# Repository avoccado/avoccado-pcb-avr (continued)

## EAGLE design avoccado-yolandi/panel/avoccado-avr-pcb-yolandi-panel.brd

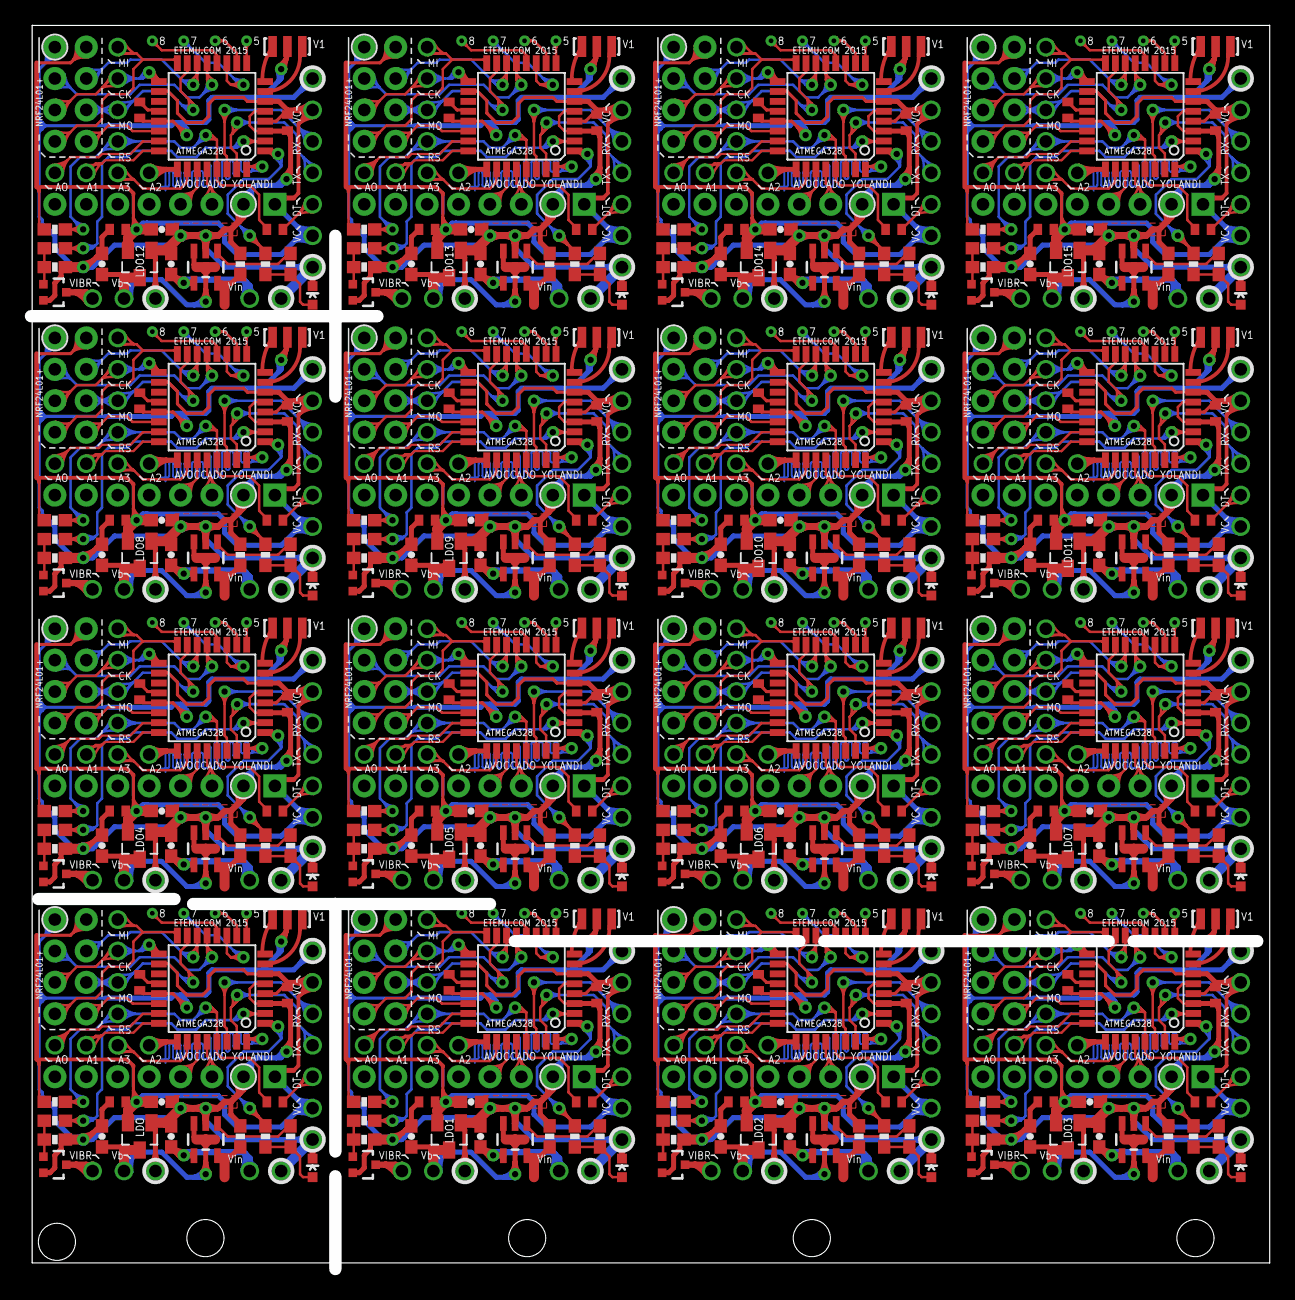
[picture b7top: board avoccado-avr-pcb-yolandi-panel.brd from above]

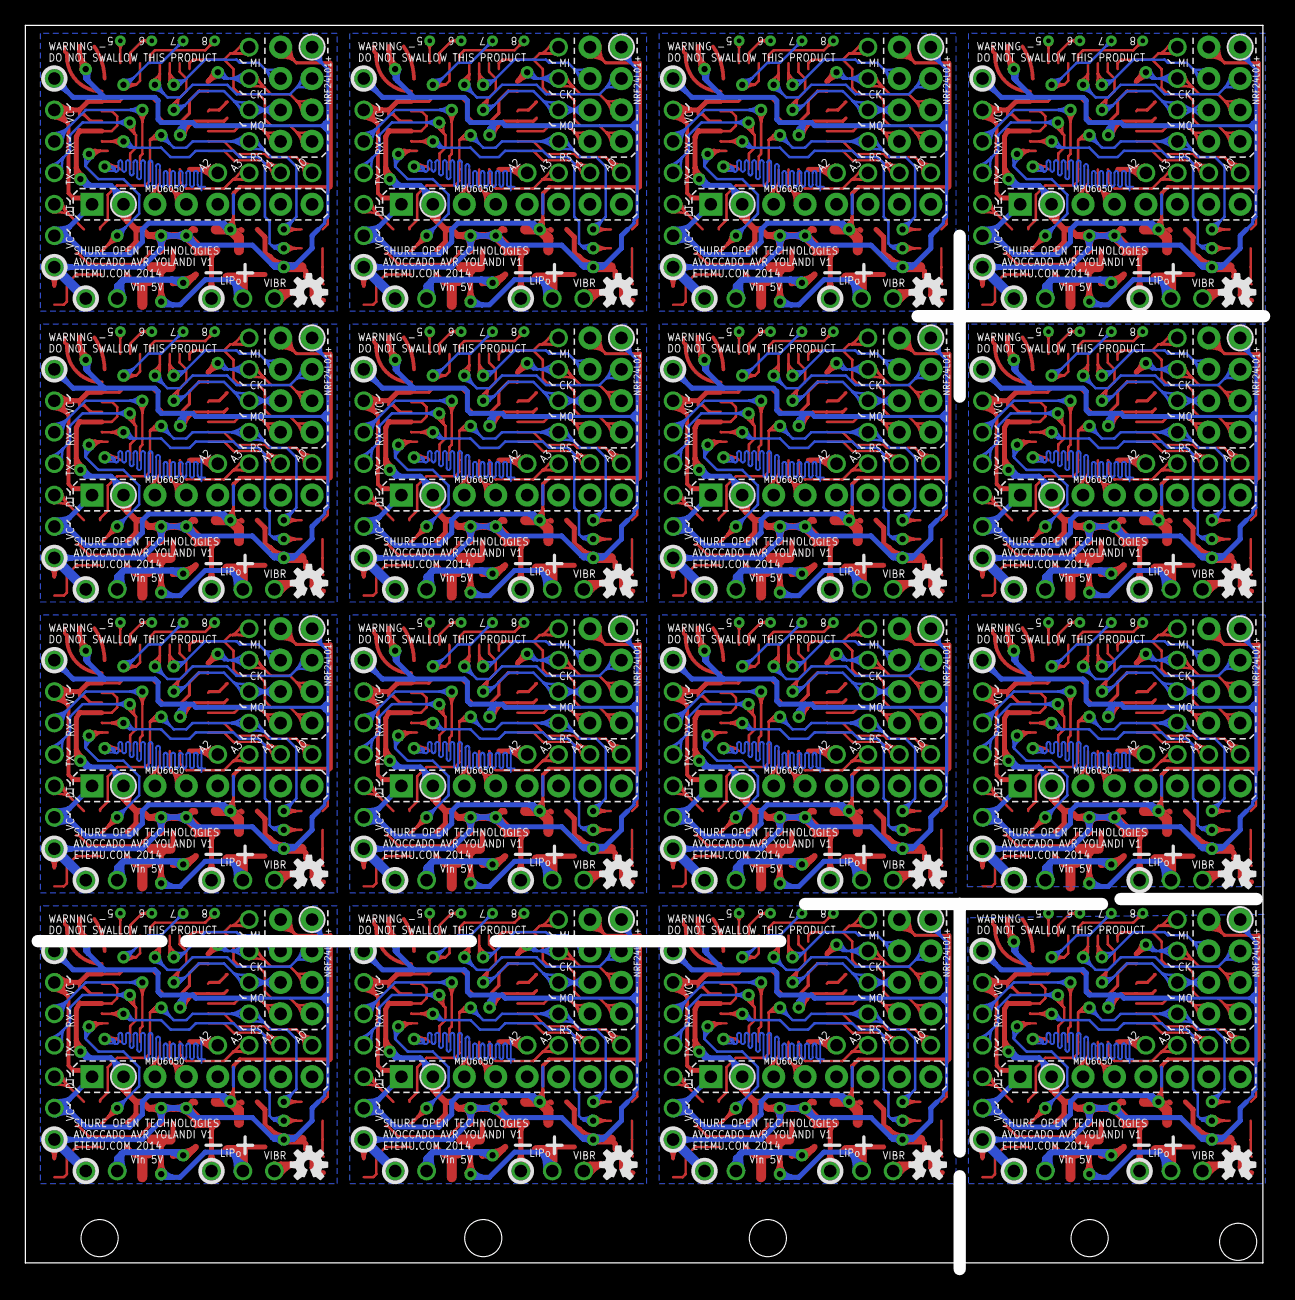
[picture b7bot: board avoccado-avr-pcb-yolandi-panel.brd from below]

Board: 2 copper layers, 99.6 x 100.0 mm, 784 parts (16 on the bottom side), 544 nets.

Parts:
AVR, AVR1, AVR2, AVR3, AVR4, AVR5, AVR6, AVR7, AVR8, AVR9, AVR10, AVR11, AVR12, AVR13, AVR14, AVR15: ATMEGA328P; TQFP32-08
C1, C2, C3, C7, C8, C9, C10, C12, C15, C16, C17, C19, C22, C23, C24, C26, C29, C30, C31, C33, C36, C37, C38, C40, C43, C44, C45, C47, C50, C51, C52, C54, C57, C58, C59, C61, C64, C65, C66, C68, C71, C72, C73, C75, C78, C79, C80, C82, C85, C86, C87, C89, C92, C93, C94, C96, C99, C100, C101, C103, C106, C107, C108, C110: 0.1uF; C0402
C4, C5, C6, C11, C13, C14, C18, C20, C21, C25, C27, C28, C32, C34, C35, C39, C41, C42, C46, C48, C49, C53, C55, C56, C60, C62, C63, C67, C69, C70, C74, C76, C77, C81, C83, C84, C88, C90, C91, C95, C97, C98, C102, C104, C105, C109, C111, C112: 4.7uF; 0603-CAP
D1, D2, D3, D4, D5, D6, D7, D8, D9, D10, D11, D12, D13, D14, D15, D16: LED; LED-0603
JP1, JP4, JP51, JP76, JP101, JP126, JP151, JP176, JP201, JP226, JP251, JP276, JP301, JP326, JP351, JP376: MPU6050; 1X08_PIN1_NO_SILK
JP2, JP27, JP28, JP29, JP47, JP48, JP49, JP50, JP72, JP73, JP74, JP75, JP97, JP98, JP99, JP100, JP122, JP123, JP124, JP125, JP147, JP148, JP149, JP150, JP172, JP173, JP174, JP175, JP197, JP198, JP199, JP200, JP222, JP223, JP224, JP225, JP247, JP248, JP249, JP250, JP272, JP273, JP274, JP275, JP297, JP298, JP299, JP300, JP322, JP323, JP324, JP325, JP347, JP348, JP349, JP350, JP372, JP373, JP374, JP375, JP397, JP398, JP399, JP400: M021X02_NO_SILK; 1X02_NO_SILK
JP3, JP5, JP6, JP7, JP8, JP9, JP10, JP11, JP12, JP13, JP14, JP15, JP16, JP17, JP18, JP19, JP20, JP21, JP22, JP23, JP24, JP25, JP26, JP30, JP31, JP32, JP33, JP34, JP35, JP36, JP37, JP38, JP39, JP40, JP41, JP42, JP43, JP44, JP45, JP46, JP52, JP53, JP54, JP55, JP56, JP57, JP58, JP59, JP60, JP61, JP62, JP63, JP64, JP65, JP66, JP67, JP68, JP69, JP70, JP71, JP77, JP78, JP79, JP80, JP81, JP82, JP83, JP84, JP85, JP86, JP87, JP88, JP89, JP90, JP91, JP92, JP93, JP94, JP95, JP96, JP102, JP103, JP104, JP105, JP106, JP107, JP108, JP109, JP110, JP111, JP112, JP113, JP114, JP115, JP116, JP117, JP118, JP119, JP120, JP121, JP127, JP128, JP129, JP130, JP131, JP132, JP133, JP134, JP135, JP136, JP137, JP138, JP139, JP140, JP141, JP142, JP143, JP144, JP145, JP146, JP152, JP153, JP154, JP155, JP156, JP157, JP158, JP159, JP160, JP161, JP162, JP163, JP164, JP165, JP166, JP167, JP168, JP169, JP170, JP171, JP177, JP178, JP179, JP180, JP181, JP182, JP183, JP184, JP185, JP186, JP187, JP188, JP189, JP190, JP191, JP192, JP193, JP194, JP195, JP196, JP202, JP203, JP204, JP205, JP206, JP207, JP208, JP209, JP210, JP211, JP212, JP213, JP214, JP215, JP216, JP217, JP218, JP219, JP220, JP221, JP227, JP228, JP229, JP230, JP231, JP232, JP233, JP234, JP235, JP236, JP237, JP238, JP239, JP240, JP241, JP242, JP243, JP244, JP245, JP246, JP252, JP253, JP254, JP255, JP256, JP257, JP258, JP259, JP260, JP261, JP262, JP263, JP264, JP265, JP266, JP267, JP268, JP269, JP270, JP271, JP277, JP278, JP279, JP280, JP281, JP282, JP283, JP284, JP285, JP286, JP287, JP288, JP289, JP290, JP291, JP292, JP293, JP294, JP295, JP296, JP302, JP303, JP304, JP305, JP306, JP307, JP308, JP309, JP310, JP311, JP312, JP313, JP314, JP315, JP316, JP317, JP318, JP319, JP320, JP321, JP327, JP328, JP329, JP330, JP331, JP332, JP333, JP334, JP335, JP336, JP337, JP338, JP339, JP340, JP341, JP342, JP343, JP344, JP345, JP346, JP352, JP353, JP354, JP355, JP356, JP357, JP358, JP359, JP360, JP361, JP362, JP363, JP364, JP365, JP366, JP367, JP368, JP369, JP370, JP371, JP377, JP378, JP379, JP380, JP381, JP382, JP383, JP384, JP385, JP386, JP387, JP388, JP389, JP390, JP391, JP392, JP393, JP394, JP395, JP396: M01NOSILK-KIT; 1X01NS-KIT
LDO, LDO1, LDO2, LDO3, LDO4, LDO5, LDO6, LDO7, LDO8, LDO9, LDO10, LDO11, LDO12, LDO13, LDO14, LDO15: MCP1703CB; SOT23
LOGO1, LOGO2, LOGO3, LOGO4, LOGO5, LOGO6, LOGO7, LOGO8, LOGO9, LOGO10, LOGO11, LOGO12, LOGO13, LOGO14, LOGO15, LOGO16: OSHW-LOGOS; OSHW-LOGO-S
Q1, Q3, Q5, Q7, Q9, Q11, Q13, Q15, Q17, Q19, Q21, Q23, Q25, Q27, Q29, Q31: 16MHz; RESONATOR-SMD
Q2, Q4, Q6, Q8, Q10, Q12, Q14, Q16, Q18, Q20, Q22, Q24, Q26, Q28, Q30, Q32: FET; SOT323
R1, R4, R6, R8, R10, R12, R14, R16, R18, R20, R22, R24, R26, R28, R30, R32, R34, R36, R38, R40, R42, R44, R46, R48, R50, R52, R54, R56, R58, R60, R62, R64, R66, R68, R70, R72, R74, R76, R78, R80, R82, R84, R86, R88, R90, R92, R94, R96: 1K; 0603-RES
R2, R7, R13, R19, R25, R31, R37, R43, R49, R55, R61, R67, R73, R79, R85, R91: 10K; 0603-RES
R3, R9, R15, R21, R27, R33, R39, R45, R51, R57, R63, R69, R75, R81, R87, R93: Rchg; 0603-RES
R5, R11, R17, R23, R29, R35, R41, R47, R53, R59, R65, R71, R77, R83, R89, R95: 1M; 0603-RES
TP1, TP2, TP3, TP4, TP5, TP6, TP7, TP8, TP9, TP10, TP11, TP12, TP13, TP14, TP15, TP16, TP17, TP18, TP19, TP20, TP21, TP22, TP23, TP24, TP25, TP26, TP27, TP28, TP29, TP30, TP31, TP32, TP33, TP34, TP35, TP36, TP37, TP38, TP39, TP40, TP41, TP42, TP43, TP44, TP45, TP46, TP47, TP48, TP49, TP50, TP51, TP52, TP53, TP54, TP55, TP56, TP57, TP58, TP59, TP60, TP61, TP62, TP63, TP64: TEST-POINTTP_15TH_THRU; TP_15TH
U1, U2, U3, U4, U5, U6, U7, U8, U9, U10, U11, U12, U13, U14, U15, U16: MCP73831; SOT23-5

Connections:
3.3V: AVR.4, AVR.6, AVR.18, C3.2, C6.1, C10.1, JP1.1, JP2.2, JP11.1, JP18.1, LDO.2, R2.2
3.3V1: AVR1.4, AVR1.6, AVR1.18, C7.1, C8.2, C14.1, JP4.1, JP31.1, JP38.1, JP47.2, LDO1.2, R7.2
3.3V2: AVR2.4, AVR2.6, AVR2.18, C15.1, C16.2, C21.1, JP51.1, JP56.1, JP63.1, JP72.2, LDO2.2, R13.2
3.3V3: AVR3.4, AVR3.6, AVR3.18, C22.1, C23.2, C28.1, JP76.1, JP81.1, JP88.1, JP97.2, LDO3.2, R19.2
3.3V4: AVR4.4, AVR4.6, AVR4.18, C29.1, C30.2, C35.1, JP101.1, JP106.1, JP113.1, JP122.2, LDO4.2, R25.2
3.3V5: AVR5.4, AVR5.6, AVR5.18, C36.1, C37.2, C42.1, JP126.1, JP131.1, JP138.1, JP147.2, LDO5.2, R31.2
3.3V6: AVR6.4, AVR6.6, AVR6.18, C43.1, C44.2, C49.1, JP151.1, JP156.1, JP163.1, JP172.2, LDO6.2, R37.2
3.3V7: AVR7.4, AVR7.6, AVR7.18, C50.1, C51.2, C56.1, JP176.1, JP181.1, JP188.1, JP197.2, LDO7.2, R43.2
3.3V8: AVR8.4, AVR8.6, AVR8.18, C57.1, C58.2, C63.1, JP201.1, JP206.1, JP213.1, JP222.2, LDO8.2, R49.2
3.3V9: AVR9.4, AVR9.6, AVR9.18, C64.1, C65.2, C70.1, JP226.1, JP231.1, JP238.1, JP247.2, LDO9.2, R55.2
3.3V10: AVR10.4, AVR10.6, AVR10.18, C71.1, C72.2, C77.1, JP251.1, JP256.1, JP263.1, JP272.2, LDO10.2, R61.2
3.3V11: AVR11.4, AVR11.6, AVR11.18, C78.1, C79.2, C84.1, JP276.1, JP281.1, JP288.1, JP297.2, LDO11.2, R67.2
3.3V12: AVR12.4, AVR12.6, AVR12.18, C85.1, C86.2, C91.1, JP301.1, JP306.1, JP313.1, JP322.2, LDO12.2, R73.2
3.3V13: AVR13.4, AVR13.6, AVR13.18, C92.1, C93.2, C98.1, JP326.1, JP331.1, JP338.1, JP347.2, LDO13.2, R79.2
3.3V14: AVR14.4, AVR14.6, AVR14.18, C99.1, C100.2, C105.1, JP351.1, JP356.1, JP363.1, JP372.2, LDO14.2, R85.2
3.3V15: AVR15.4, AVR15.6, AVR15.18, C106.1, C107.2, C112.1, JP376.1, JP381.1, JP388.1, JP397.2, LDO15.2, R91.2
5V: C4.1, JP17.1, U2.4
5V1: C11.1, JP37.1, U1.4
5V2: C18.1, JP62.1, U3.4
5V3: C25.1, JP87.1, U4.4
5V4: C32.1, JP112.1, U5.4
5V5: C39.1, JP137.1, U6.4
5V6: C46.1, JP162.1, U7.4
5V7: C53.1, JP187.1, U8.4
5V8: C60.1, JP212.1, U9.4
5V9: C67.1, JP237.1, U10.4
5V10: C74.1, JP262.1, U11.4
5V11: C81.1, JP287.1, U12.4
5V12: C88.1, JP312.1, U13.4
5V13: C95.1, JP337.1, U14.4
5V14: C102.1, JP362.1, U15.4
5V15: C109.1, JP387.1, U16.4
A0: AVR.23, JP19.1
A1: AVR.24, JP20.1
A2: AVR.25, JP21.1
A3: AVR.26, JP22.1
A4: AVR.27, JP1.4
A5: AVR.28, JP1.3
A7: AVR1.28, JP4.3
A7-NRF-IRQ: AVR.22, JP29.2
A7-NRF-IRQ1: AVR1.22, JP50.2
A7-NRF-IRQ2: AVR2.22, JP75.2
A7-NRF-IRQ3: AVR3.22, JP100.2
A7-NRF-IRQ4: AVR4.22, JP125.2
A7-NRF-IRQ5: AVR5.22, JP150.2
A7-NRF-IRQ6: AVR6.22, JP175.2
A7-NRF-IRQ7: AVR7.22, JP200.2
A7-NRF-IRQ8: AVR8.22, JP225.2
A7-NRF-IRQ9: AVR9.22, JP250.2
A7-NRF-IRQ10: AVR10.22, JP275.2
A7-NRF-IRQ11: AVR11.22, JP300.2
A7-NRF-IRQ12: AVR12.22, JP325.2
A7-NRF-IRQ13: AVR13.22, JP350.2
A7-NRF-IRQ14: AVR14.22, JP375.2
A7-NRF-IRQ15: AVR15.22, JP400.2
A8: AVR1.27, JP4.4
A9: AVR1.26, JP42.1
A10: AVR1.25, JP41.1
A11: AVR1.24, JP40.1
A12: AVR1.23, JP39.1
A14: AVR2.28, JP51.3
A15: AVR2.27, JP51.4
A16: AVR2.26, JP67.1
A17: AVR2.25, JP66.1
A18: AVR2.24, JP65.1
A19: AVR2.23, JP64.1
A21: AVR3.28, JP76.3
A22: AVR3.27, JP76.4
A23: AVR3.26, JP92.1
A24: AVR3.25, JP91.1
A25: AVR3.24, JP90.1
A26: AVR3.23, JP89.1
A28: AVR4.28, JP101.3
A29: AVR4.27, JP101.4
A30: AVR4.26, JP117.1
A31: AVR4.25, JP116.1
A32: AVR4.24, JP115.1
A33: AVR4.23, JP114.1
A35: AVR5.28, JP126.3
A36: AVR5.27, JP126.4
A37: AVR5.26, JP142.1
A38: AVR5.25, JP141.1
A39: AVR5.24, JP140.1
A40: AVR5.23, JP139.1
A42: AVR6.28, JP151.3
A43: AVR6.27, JP151.4
A44: AVR6.26, JP167.1
A45: AVR6.25, JP166.1
A46: AVR6.24, JP165.1
A47: AVR6.23, JP164.1
A49: AVR7.28, JP176.3
A50: AVR7.27, JP176.4
A51: AVR7.26, JP192.1
A52: AVR7.25, JP191.1
A53: AVR7.24, JP190.1
A54: AVR7.23, JP189.1
A56: AVR8.28, JP201.3
A57: AVR8.27, JP201.4
A58: AVR8.26, JP217.1
A59: AVR8.25, JP216.1
A60: AVR8.24, JP215.1
A61: AVR8.23, JP214.1
A63: AVR9.28, JP226.3
A64: AVR9.27, JP226.4
A65: AVR9.26, JP242.1
A66: AVR9.25, JP241.1
A67: AVR9.24, JP240.1
A68: AVR9.23, JP239.1
A70: AVR10.28, JP251.3
A71: AVR10.27, JP251.4
A72: AVR10.26, JP267.1
A73: AVR10.25, JP266.1
A74: AVR10.24, JP265.1
A75: AVR10.23, JP264.1
A77: AVR11.28, JP276.3
A78: AVR11.27, JP276.4
A79: AVR11.26, JP292.1
A80: AVR11.25, JP291.1
A81: AVR11.24, JP290.1
A82: AVR11.23, JP289.1
A84: AVR12.28, JP301.3
A85: AVR12.27, JP301.4
A86: AVR12.26, JP317.1
A87: AVR12.25, JP316.1
A88: AVR12.24, JP315.1
A89: AVR12.23, JP314.1
A91: AVR13.28, JP326.3
A92: AVR13.27, JP326.4
A93: AVR13.26, JP342.1
A94: AVR13.25, JP341.1
A95: AVR13.24, JP340.1
A96: AVR13.23, JP339.1
A98: AVR14.28, JP351.3
A99: AVR14.27, JP351.4
A100: AVR14.26, JP367.1
A101: AVR14.25, JP366.1
A102: AVR14.24, JP365.1
A103: AVR14.23, JP364.1
A105: AVR15.28, JP376.3
A106: AVR15.27, JP376.4
A107: AVR15.26, JP392.1
A108: AVR15.25, JP391.1
A109: AVR15.24, JP390.1
A110: AVR15.23, JP389.1
AREF: AVR.20, C1.2
AREF1: AVR1.20, C9.2
AREF2: AVR2.20, C17.2
AREF3: AVR3.20, C24.2
AREF4: AVR4.20, C31.2
AREF5: AVR5.20, C38.2
AREF6: AVR6.20, C45.2
AREF7: AVR7.20, C52.2
AREF8: AVR8.20, C59.2
AREF9: AVR9.20, C66.2
AREF10: AVR10.20, C73.2
AREF11: AVR11.20, C80.2
AREF12: AVR12.20, C87.2
AREF13: AVR13.20, C94.2
AREF14: AVR14.20, C101.2
AREF15: AVR15.20, C108.2
CHG-PROG: R3.2, U2.5
CHG-PROG1: R9.2, U1.5
CHG-PROG2: R15.2, U3.5
CHG-PROG3: R21.2, U4.5
CHG-PROG4: R27.2, U5.5
CHG-PROG5: R33.2, U6.5
CHG-PROG6: R39.2, U7.5
CHG-PROG7: R45.2, U8.5
CHG-PROG8: R51.2, U9.5
CHG-PROG9: R57.2, U10.5
CHG-PROG10: R63.2, U11.5
CHG-PROG11: R69.2, U12.5
CHG-PROG12: R75.2, U13.5
CHG-PROG13: R81.2, U14.5
CHG-PROG14: R87.2, U15.5
CHG-PROG15: R93.2, U16.5
D1: AVR1.13, JP48.1
D3: AVR.1, R6.1
D4: AVR.2, R1.1
D5: AVR.9, TP1.P$1
D6: AVR.10, TP6.P$1
D7: AVR.11, TP7.P$1
D8: AVR.12, TP8.P$1
D9: AVR.13, JP27.1
D10: AVR.14, JP27.2
D11: AVR1.12, TP5.P$1
D13: AVR1.1, R12.1
D14: AVR1.2, R8.1
D15: AVR1.9, TP2.P$1
D16: AVR1.10, TP3.P$1
D17: AVR1.11, TP4.P$1
D18: AVR1.14, JP48.2
D19: AVR2.13, JP73.1
D20: AVR2.12, TP12.P$1
D22: AVR2.1, R18.1
D23: AVR2.2, R14.1
D24: AVR2.9, TP9.P$1
D25: AVR2.10, TP10.P$1
D26: AVR2.11, TP11.P$1
D27: AVR2.14, JP73.2
D28: AVR3.13, JP98.1
D29: AVR3.12, TP16.P$1
D31: AVR3.1, R24.1
D32: AVR3.2, R20.1
D33: AVR3.9, TP13.P$1
D34: AVR3.10, TP14.P$1
D35: AVR3.11, TP15.P$1
D36: AVR3.14, JP98.2
D37: AVR4.13, JP123.1
D38: AVR4.12, TP20.P$1
D40: AVR4.1, R30.1
D41: AVR4.2, R26.1
D42: AVR4.9, TP17.P$1
D43: AVR4.10, TP18.P$1
D44: AVR4.11, TP19.P$1
D45: AVR4.14, JP123.2
D46: AVR5.13, JP148.1
D47: AVR5.12, TP24.P$1
D49: AVR5.1, R36.1
D50: AVR5.2, R32.1
D51: AVR5.9, TP21.P$1
D52: AVR5.10, TP22.P$1
D53: AVR5.11, TP23.P$1
D54: AVR5.14, JP148.2
D55: AVR6.13, JP173.1
D56: AVR6.12, TP28.P$1
D58: AVR6.1, R42.1
D59: AVR6.2, R38.1
D60: AVR6.9, TP25.P$1
D61: AVR6.10, TP26.P$1
D62: AVR6.11, TP27.P$1
D63: AVR6.14, JP173.2
D64: AVR7.13, JP198.1
D65: AVR7.12, TP32.P$1
D67: AVR7.1, R48.1
D68: AVR7.2, R44.1
D69: AVR7.9, TP29.P$1
D70: AVR7.10, TP30.P$1
D71: AVR7.11, TP31.P$1
D72: AVR7.14, JP198.2
D73: AVR8.13, JP223.1
D74: AVR8.12, TP36.P$1
D76: AVR8.1, R54.1
D77: AVR8.2, R50.1
D78: AVR8.9, TP33.P$1
D79: AVR8.10, TP34.P$1
D80: AVR8.11, TP35.P$1
D81: AVR8.14, JP223.2
D82: AVR9.13, JP248.1
D83: AVR9.12, TP40.P$1
D85: AVR9.1, R60.1
D86: AVR9.2, R56.1
D87: AVR9.9, TP37.P$1
D88: AVR9.10, TP38.P$1
D89: AVR9.11, TP39.P$1
D90: AVR9.14, JP248.2
D91: AVR10.13, JP273.1
D92: AVR10.12, TP44.P$1
D94: AVR10.1, R66.1
D95: AVR10.2, R62.1
D96: AVR10.9, TP41.P$1
D97: AVR10.10, TP42.P$1
D98: AVR10.11, TP43.P$1
D99: AVR10.14, JP273.2
D100: AVR11.13, JP298.1
D101: AVR11.12, TP48.P$1
D103: AVR11.1, R72.1
D104: AVR11.2, R68.1
D105: AVR11.9, TP45.P$1
D106: AVR11.10, TP46.P$1
D107: AVR11.11, TP47.P$1
D108: AVR11.14, JP298.2
D109: AVR12.13, JP323.1
D110: AVR12.12, TP52.P$1
D112: AVR12.1, R78.1
D113: AVR12.2, R74.1
D114: AVR12.9, TP49.P$1
D115: AVR12.10, TP50.P$1
D116: AVR12.11, TP51.P$1
D117: AVR12.14, JP323.2
D118: AVR13.13, JP348.1
D119: AVR13.12, TP56.P$1
D121: AVR13.1, R84.1
D122: AVR13.2, R80.1
D123: AVR13.9, TP53.P$1
D124: AVR13.10, TP54.P$1
D125: AVR13.11, TP55.P$1
D126: AVR13.14, JP348.2
D127: AVR14.13, JP373.1
D128: AVR14.12, TP60.P$1
D130: AVR14.1, R90.1
D131: AVR14.2, R86.1
D132: AVR14.9, TP57.P$1
D133: AVR14.10, TP58.P$1
D134: AVR14.11, TP59.P$1
D135: AVR14.14, JP373.2
D136: AVR15.13, JP398.1
D137: AVR15.12, TP64.P$1
D139: AVR15.1, R96.1
D140: AVR15.2, R92.1
D141: AVR15.9, TP61.P$1
D142: AVR15.10, TP62.P$1
D143: AVR15.11, TP63.P$1
D144: AVR15.14, JP398.2
DTR: C2.2, JP10.1
DTR1: C12.2, JP30.1
DTR2: C19.2, JP55.1
DTR3: C26.2, JP80.1
DTR4: C33.2, JP105.1
DTR5: C40.2, JP130.1
DTR6: C47.2, JP155.1
DTR7: C54.2, JP180.1
DTR8: C61.2, JP205.1
DTR9: C68.2, JP230.1
DTR10: C75.2, JP255.1
DTR11: C82.2, JP280.1
DTR12: C89.2, JP305.1
DTR13: C96.2, JP330.1
DTR14: C103.2, JP355.1
DTR15: C110.2, JP380.1
GND: AVR.3, AVR.5, AVR.21, C1.1, C3.1, C4.2, C5.2, C6.2, C10.2, D1.C, JP1.2, JP2.1, JP3.1, JP6.1, JP25.1, JP26.1, LDO.1, Q1.2, Q2.2, R3.1, R5.1, U2.2
GND1: AVR1.3, AVR1.5, AVR1.21, C7.2, C8.1, C9.1, C11.2, C13.2, C14.2, D2.C, JP4.2, JP5.1, JP36.1, JP45.1, JP46.1, JP47.1, LDO1.1, Q3.2, Q4.2, R9.1, R11.1, U1.2
GND2: AVR2.3, AVR2.5, AVR2.21, C15.2, C16.1, C17.1, C18.2, C20.2, C21.2, D3.C, JP51.2, JP52.1, JP61.1, JP70.1, JP71.1, JP72.1, LDO2.1, Q5.2, Q6.2, R15.1, R17.1, U3.2
GND3: AVR3.3, AVR3.5, AVR3.21, C22.2, C23.1, C24.1, C25.2, C27.2, C28.2, D4.C, JP76.2, JP77.1, JP86.1, JP95.1, JP96.1, JP97.1, LDO3.1, Q7.2, Q8.2, R21.1, R23.1, U4.2
GND4: AVR4.3, AVR4.5, AVR4.21, C29.2, C30.1, C31.1, C32.2, C34.2, C35.2, D5.C, JP101.2, JP102.1, JP111.1, JP120.1, JP121.1, JP122.1, LDO4.1, Q9.2, Q10.2, R27.1, R29.1, U5.2
GND5: AVR5.3, AVR5.5, AVR5.21, C36.2, C37.1, C38.1, C39.2, C41.2, C42.2, D6.C, JP126.2, JP127.1, JP136.1, JP145.1, JP146.1, JP147.1, LDO5.1, Q11.2, Q12.2, R33.1, R35.1, U6.2
GND6: AVR6.3, AVR6.5, AVR6.21, C43.2, C44.1, C45.1, C46.2, C48.2, C49.2, D7.C, JP151.2, JP152.1, JP161.1, JP170.1, JP171.1, JP172.1, LDO6.1, Q13.2, Q14.2, R39.1, R41.1, U7.2
GND7: AVR7.3, AVR7.5, AVR7.21, C50.2, C51.1, C52.1, C53.2, C55.2, C56.2, D8.C, JP176.2, JP177.1, JP186.1, JP195.1, JP196.1, JP197.1, LDO7.1, Q15.2, Q16.2, R45.1, R47.1, U8.2
GND8: AVR8.3, AVR8.5, AVR8.21, C57.2, C58.1, C59.1, C60.2, C62.2, C63.2, D9.C, JP201.2, JP202.1, JP211.1, JP220.1, JP221.1, JP222.1, LDO8.1, Q17.2, Q18.2, R51.1, R53.1, U9.2
GND9: AVR9.3, AVR9.5, AVR9.21, C64.2, C65.1, C66.1, C67.2, C69.2, C70.2, D10.C, JP226.2, JP227.1, JP236.1, JP245.1, JP246.1, JP247.1, LDO9.1, Q19.2, Q20.2, R57.1, R59.1, U10.2
GND10: AVR10.3, AVR10.5, AVR10.21, C71.2, C72.1, C73.1, C74.2, C76.2, C77.2, D11.C, JP251.2, JP252.1, JP261.1, JP270.1, JP271.1, JP272.1, LDO10.1, Q21.2, Q22.2, R63.1, R65.1, U11.2
GND11: AVR11.3, AVR11.5, AVR11.21, C78.2, C79.1, C80.1, C81.2, C83.2, C84.2, D12.C, JP276.2, JP277.1, JP286.1, JP295.1, JP296.1, JP297.1, LDO11.1, Q23.2, Q24.2, R69.1, R71.1, U12.2
GND12: AVR12.3, AVR12.5, AVR12.21, C85.2, C86.1, C87.1, C88.2, C90.2, C91.2, D13.C, JP301.2, JP302.1, JP311.1, JP320.1, JP321.1, JP322.1, LDO12.1, Q25.2, Q26.2, R75.1, R77.1, U13.2
GND13: AVR13.3, AVR13.5, AVR13.21, C92.2, C93.1, C94.1, C95.2, C97.2, C98.2, D14.C, JP326.2, JP327.1, JP336.1, JP345.1, JP346.1, JP347.1, LDO13.1, Q27.2, Q28.2, R81.1, R83.1, U14.2
GND14: AVR14.3, AVR14.5, AVR14.21, C99.2, C100.1, C101.1, C102.2, C104.2, C105.2, D15.C, JP351.2, JP352.1, JP361.1, JP370.1, JP371.1, JP372.1, LDO14.1, Q29.2, Q30.2, R87.1, R89.1, U15.2
GND15: AVR15.3, AVR15.5, AVR15.21, C106.2, C107.1, C108.1, C109.2, C111.2, C112.2, D16.C, JP376.2, JP377.1, JP386.1, JP395.1, JP396.1, JP397.1, LDO15.1, Q31.2, Q32.2, R93.1, R95.1, U16.2
LED: D1.A, R4.1, R6.2
LED1: D2.A, R10.1, R12.2
LED2: D3.A, R16.1, R18.2
LED3: D4.A, R22.1, R24.2
LED4: D5.A, R28.1, R30.2
LED5: D6.A, R34.1, R36.2
LED6: D7.A, R40.1, R42.2
LED7: D8.A, R46.1, R48.2
LED8: D9.A, R52.1, R54.2
LED9: D10.A, R58.1, R60.2
LED10: D11.A, R64.1, R66.2
LED11: D12.A, R70.1, R72.2
LED12: D13.A, R76.1, R78.2
LED13: D14.A, R82.1, R84.2
LED14: D15.A, R88.1, R90.2
LED15: D16.A, R94.1, R96.2
MISO: AVR.16, JP12.1, JP29.1
MISO1: AVR1.16, JP32.1, JP50.1
MISO2: AVR2.16, JP57.1, JP75.1
MISO3: AVR3.16, JP82.1, JP100.1
MISO4: AVR4.16, JP107.1, JP125.1
MISO5: AVR5.16, JP132.1, JP150.1
MISO6: AVR6.16, JP157.1, JP175.1
MISO7: AVR7.16, JP182.1, JP200.1
MISO8: AVR8.16, JP207.1, JP225.1
MISO9: AVR9.16, JP232.1, JP250.1
MISO10: AVR10.16, JP257.1, JP275.1
MISO11: AVR11.16, JP282.1, JP300.1
MISO12: AVR12.16, JP307.1, JP325.1
MISO13: AVR13.16, JP332.1, JP350.1
MISO14: AVR14.16, JP357.1, JP375.1
MISO15: AVR15.16, JP382.1, JP400.1
MOSI: AVR.15, JP14.1, JP28.2
MOSI1: AVR1.15, JP34.1, JP49.2
MOSI2: AVR2.15, JP59.1, JP74.2
MOSI3: AVR3.15, JP84.1, JP99.2
MOSI4: AVR4.15, JP109.1, JP124.2
MOSI5: AVR5.15, JP134.1, JP149.2
MOSI6: AVR6.15, JP159.1, JP174.2
MOSI7: AVR7.15, JP184.1, JP199.2
MOSI8: AVR8.15, JP209.1, JP224.2
MOSI9: AVR9.15, JP234.1, JP249.2
MOSI10: AVR10.15, JP259.1, JP274.2
MOSI11: AVR11.15, JP284.1, JP299.2
MOSI12: AVR12.15, JP309.1, JP324.2
MOSI13: AVR13.15, JP334.1, JP349.2
MOSI14: AVR14.15, JP359.1, JP374.2
MOSI15: AVR15.15, JP384.1, JP399.2
unnamed: AVR.8, Q1.1
unnamed: AVR.7, Q1.3
unnamed: AVR1.8, Q3.1
unnamed: AVR1.7, Q3.3
unnamed: Q4.1, R8.2, R11.2
unnamed: Q2.1, R1.2, R5.2
unnamed: AVR2.8, Q5.1
unnamed: AVR2.7, Q5.3
unnamed: Q6.1, R14.2, R17.2
unnamed: AVR3.8, Q7.1
unnamed: AVR3.7, Q7.3
unnamed: Q8.1, R20.2, R23.2
unnamed: AVR4.8, Q9.1
unnamed: AVR4.7, Q9.3
unnamed: Q10.1, R26.2, R29.2
unnamed: AVR5.8, Q11.1
unnamed: AVR5.7, Q11.3
unnamed: Q12.1, R32.2, R35.2
unnamed: AVR6.8, Q13.1
unnamed: AVR6.7, Q13.3
unnamed: Q14.1, R38.2, R41.2
unnamed: AVR7.8, Q15.1
unnamed: AVR7.7, Q15.3
unnamed: Q16.1, R44.2, R47.2
unnamed: AVR8.8, Q17.1
unnamed: AVR8.7, Q17.3
unnamed: Q18.1, R50.2, R53.2
unnamed: AVR9.8, Q19.1
unnamed: AVR9.7, Q19.3
unnamed: Q20.1, R56.2, R59.2
unnamed: AVR10.8, Q21.1
unnamed: AVR10.7, Q21.3
unnamed: Q22.1, R62.2, R65.2
unnamed: AVR11.8, Q23.1
unnamed: AVR11.7, Q23.3
unnamed: Q24.1, R68.2, R71.2
unnamed: AVR12.8, Q25.1
unnamed: AVR12.7, Q25.3
unnamed: Q26.1, R74.2, R77.2
unnamed: AVR13.8, Q27.1
unnamed: AVR13.7, Q27.3
unnamed: Q28.1, R80.2, R83.2
unnamed: AVR14.8, Q29.1
unnamed: AVR14.7, Q29.3
unnamed: Q30.1, R86.2, R89.2
unnamed: AVR15.8, Q31.1
unnamed: AVR15.7, Q31.3
unnamed: Q32.1, R92.2, R95.2
RESET: AVR.29, C2.1, JP15.1, R2.1
RESET1: AVR1.29, C12.1, JP35.1, R7.1
RESET2: AVR2.29, C19.1, JP60.1, R13.1
RESET3: AVR3.29, C26.1, JP85.1, R19.1
RESET4: AVR4.29, C33.1, JP110.1, R25.1
RESET5: AVR5.29, C40.1, JP135.1, R31.1
RESET6: AVR6.29, C47.1, JP160.1, R37.1
RESET7: AVR7.29, C54.1, JP185.1, R43.1
RESET8: AVR8.29, C61.1, JP210.1, R49.1
RESET9: AVR9.29, C68.1, JP235.1, R55.1
RESET10: AVR10.29, C75.1, JP260.1, R61.1
RESET11: AVR11.29, C82.1, JP285.1, R67.1
RESET12: AVR12.29, C89.1, JP310.1, R73.1
RESET13: AVR13.29, C96.1, JP335.1, R79.1
RESET14: AVR14.29, C103.1, JP360.1, R85.1
RESET15: AVR15.29, C110.1, JP385.1, R91.1
RXI: AVR.30, JP8.1
RXI1: AVR1.30, JP7.1
RXI2: AVR2.30, JP53.1
RXI3: AVR3.30, JP78.1
RXI4: AVR4.30, JP103.1
RXI5: AVR5.30, JP128.1
RXI6: AVR6.30, JP153.1
RXI7: AVR7.30, JP178.1
RXI8: AVR8.30, JP203.1
RXI9: AVR9.30, JP228.1
RXI10: AVR10.30, JP253.1
RXI11: AVR11.30, JP278.1
RXI12: AVR12.30, JP303.1
RXI13: AVR13.30, JP328.1
RXI14: AVR14.30, JP353.1
RXI15: AVR15.30, JP378.1
SCK: AVR.17, JP13.1, JP28.1
SCK1: AVR1.17, JP33.1, JP49.1
SCK2: AVR2.17, JP58.1, JP74.1
SCK3: AVR3.17, JP83.1, JP99.1
SCK4: AVR4.17, JP108.1, JP124.1
SCK5: AVR5.17, JP133.1, JP149.1
SCK6: AVR6.17, JP158.1, JP174.1
SCK7: AVR7.17, JP183.1, JP199.1
SCK8: AVR8.17, JP208.1, JP224.1
SCK9: AVR9.17, JP233.1, JP249.1
SCK10: AVR10.17, JP258.1, JP274.1
SCK11: AVR11.17, JP283.1, JP299.1
SCK12: AVR12.17, JP308.1, JP324.1
SCK13: AVR13.17, JP333.1, JP349.1
SCK14: AVR14.17, JP358.1, JP374.1
SCK15: AVR15.17, JP383.1, JP399.1
SOC: R4.2, U2.1
SOC1: R10.2, U1.1
SOC2: R16.2, U3.1
SOC3: R22.2, U4.1
SOC4: R28.2, U5.1
SOC5: R34.2, U6.1
SOC6: R40.2, U7.1
SOC7: R46.2, U8.1
SOC8: R52.2, U9.1
SOC9: R58.2, U10.1
SOC10: R64.2, U11.1
SOC11: R70.2, U12.1
SOC12: R76.2, U13.1
SOC13: R82.2, U14.1
SOC14: R88.2, U15.1
SOC15: R94.2, U16.1
TXO: AVR.31, JP9.1
TXO1: AVR1.31, JP16.1
TXO2: AVR2.31, JP54.1
TXO3: AVR3.31, JP79.1
TXO4: AVR4.31, JP104.1
TXO5: AVR5.31, JP129.1
TXO6: AVR6.31, JP154.1
TXO7: AVR7.31, JP179.1
TXO8: AVR8.31, JP204.1
TXO9: AVR9.31, JP229.1
TXO10: AVR10.31, JP254.1
TXO11: AVR11.31, JP279.1
TXO12: AVR12.31, JP304.1
TXO13: AVR13.31, JP329.1
TXO14: AVR14.31, JP354.1
TXO15: AVR15.31, JP379.1
VBAT: C5.1, JP24.1, LDO.3, U2.3
VBAT1: C13.1, JP43.1, LDO1.3, U1.3
VBAT2: C20.1, JP68.1, LDO2.3, U3.3
VBAT3: C27.1, JP93.1, LDO3.3, U4.3
VBAT4: C34.1, JP118.1, LDO4.3, U5.3
VBAT5: C41.1, JP143.1, LDO5.3, U6.3
VBAT6: C48.1, JP168.1, LDO6.3, U7.3
VBAT7: C55.1, JP193.1, LDO7.3, U8.3
VBAT8: C62.1, JP218.1, LDO8.3, U9.3
VBAT9: C69.1, JP243.1, LDO9.3, U10.3
VBAT10: C76.1, JP268.1, LDO10.3, U11.3
VBAT11: C83.1, JP293.1, LDO11.3, U12.3
VBAT12: C90.1, JP318.1, LDO12.3, U13.3
VBAT13: C97.1, JP343.1, LDO13.3, U14.3
VBAT14: C104.1, JP368.1, LDO14.3, U15.3
VBAT15: C111.1, JP393.1, LDO15.3, U16.3
VIBR: JP23.1, Q2.3
VIBR1: JP44.1, Q4.3
VIBR2: JP69.1, Q6.3
VIBR3: JP94.1, Q8.3
VIBR4: JP119.1, Q10.3
VIBR5: JP144.1, Q12.3
VIBR6: JP169.1, Q14.3
VIBR7: JP194.1, Q16.3
VIBR8: JP219.1, Q18.3
VIBR9: JP244.1, Q20.3
VIBR10: JP269.1, Q22.3
VIBR11: JP294.1, Q24.3
VIBR12: JP319.1, Q26.3
VIBR13: JP344.1, Q28.3
VIBR14: JP369.1, Q30.3
VIBR15: JP394.1, Q32.3

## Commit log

2014-11-28 initial push from local repo
2014-11-30 add n-chan LL mosfet for vibrator
2014-11-30 add A6 and A7 analog inputs
2014-11-30 fix fragmented move
2014-12-01 wip change to SMD headers
2014-12-03 evaluating SMD pads
2014-12-03 exchanged THT pin rows for custom SMD pads
2014-12-04 squeezed the headers together to make the PCB even thinner
2014-12-04 add NRF24 header wip
2014-12-06 reroute NRF24 header with bottom layer, add MPU6050 satellite board
2014-12-06 route MPU6050 header
2014-12-06 rewire filter caps
2014-12-06 white silkscreen fills at GND pads
2014-12-06 add QFN package for MCU wip
2014-12-06 moved Xtal to make room for vias
2014-12-07 charge indicator wired to MCU
2014-12-07 reroute bottom header, reduce airwires
2014-12-07 minor corrections
2014-12-07 reroute GND layer, ditch pins 2&3
2014-12-07 corrected DRC errors, mostly spacing
2014-12-08 USB bootloader
2014-12-09 increase board size to 19x42
2014-12-09 change MPU6050 locked header to straight one
2014-12-09 silkscreen placed
2014-12-10 3D renderings and micro version started
2014-12-11 render gerber files and update micro-a1
2014-12-11 finish avoccado-avr-pcb-kane micro version
2014-12-11 cleanup
2014-12-13 add board screenshot
2015-01-02 start new 1 sq inch PCB fork 'yolandi'
2015-01-03 routing yolandi
    added DTR-reset latch circuit with 0.1uF C
2015-01-03 routing yolandi, lower part with PDU
2015-01-03 routing the buffered load output
2015-01-03 wip yolandi
2015-01-03 wip add silkscreen
2015-01-03 wip silkscreen
2015-01-03 change pkg of NRF24 header to round pins
2015-01-03 schematic cleanup
2015-01-03 bottom silkscreen
2015-01-04 shrink dimensions 1mm
2015-01-04 clear silkscreen which is outside of dimension layer
2015-01-04 silkscreen component values
2015-01-04 m silkscreen
2015-01-05 draft: panelized yolandi to 100x100mm
2015-01-06 Nora: new PCB with plated half holes for surface mounting
2015-01-06 fix silkscreen on nora
2015-01-07 add rectangles at plated half holes
2015-01-10 panelized nora to 50x50mm²
2015-01-14 panelized nora2, rendered gerbers
2015-01-17 create test jig for nora
2015-01-17 switch layer for ICSP 2x5 header to bottom
2015-01-17 ditch DTR line at ICSP header
2015-01-17 pour gnd
2015-01-18 test alignment of test jig panel
2015-01-21 naming scheme
2015-01-25 consistent naming
2015-01-28 Initial commit for Avoccado° Faye
    new: battery voltage sensing
2015-01-28 ditching not connected pins from MPU board
2015-01-28 redesign lower half of Faye
2015-01-28 rerouting bottom half
2015-01-28 rerouting bottom half WIP
2015-01-29 bottom WIP
2015-01-29 reroute filter C top right
2015-01-29 all signals routed to spec
    TODO: snap to grid, silkscreen
2015-01-29 pour top GND polygon
2015-01-31 change footprint of mosfet to sot23-3
2015-02-02 bigger pads for test jig, g-code for solder stencils
2015-02-08 micro usb on the bottom
2015-02-10 route USB connector, additional headers
2015-02-11 add test points
2015-02-11 spread 0402 resistors
2015-02-11 new: all headers on 100mil grid
2015-02-12 render 2d preview image
2015-02-12 spacing of resonator slightly larger
2015-02-12 update PNG rendering of Faye
2015-02-12 milling paths ready for matrix panelizing
2015-02-12 color scheme
2015-02-27 Faye: adjusted Rs, new PCB: Felina
    Felina is a larger PCB with the MPU6050 on board instead of a breakout
    board.
2015-02-28 Felina: rearrange and start to route
2015-02-28 route 3V3
2015-02-28 move RST pullup away from bottom left
2015-02-28 Vcc and GND routed at bottom
2015-02-28 route reset pullup
2015-03-01 no airwires left :+1: :shaved_ice:
2015-03-01 Add Felina
2015-03-01 cleanup schematics, add fiducials
2015-03-01 fix DRC errors
2015-03-01 add Felina fork with screw holes
2015-03-01 daisy chainable tab layout
2015-03-02 render schematic PNG
2015-03-08 ditch right mounting holes, rearrange USB
2015-03-08 new footprint for USB
2015-03-08 eliminated redundant 0402 Rs for Rp
2015-03-08 no airwires left, added 5V USB power LED
2015-03-08 add A° tag
2015-03-08 add redundant fiducials near mounting holes, reverse LED and R
2015-03-09 increase trace width for Vcc near edges
2015-03-09 rearrange board for panelization
2015-03-11 Introducing Avoccado° Gin: Nano version, QFN only, not obeing placement restrictions, board dimensions less than one NRF24L01+ module.
2015-03-12 add USB socket (without data lines)
2015-03-13 cleanup unused headers
2015-03-22 add RX and TX test points
2015-03-23 no airwires left :shipit:
2015-03-25 add SMD pads to bottom layer
2015-03-25 Finish silkscreen with a wide A° instead of pin declarations
2015-03-26 render PNG preview
2015-03-26 DRC check with 6mil / 6mil, silkscreen touchup
2015-03-26 Felina: remove screw mounts, Gin: prepare to panelize
2015-03-26 fix big silkscreen logo
2015-03-26 layout panel with Gin, Felina, Faye at 100x100mm²
2015-03-27 Gin: fix mirrored silkscreen on bottom layer
2015-03-28 add PCBs with ICSP adapters and panelize
2015-03-28 minor touchup, render gerber files
2015-03-28 render PNGs
2015-03-28 del unused mask for fiducials
2015-03-28 add Gin
